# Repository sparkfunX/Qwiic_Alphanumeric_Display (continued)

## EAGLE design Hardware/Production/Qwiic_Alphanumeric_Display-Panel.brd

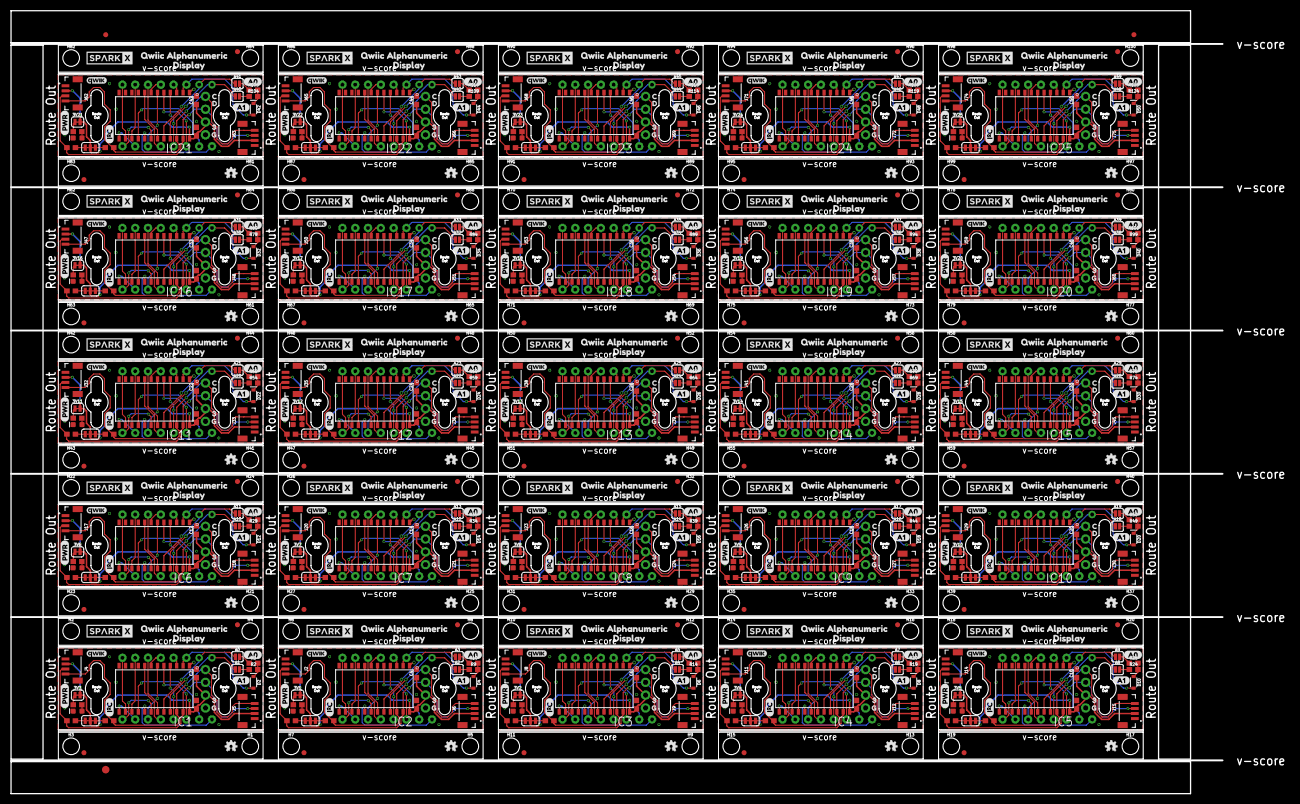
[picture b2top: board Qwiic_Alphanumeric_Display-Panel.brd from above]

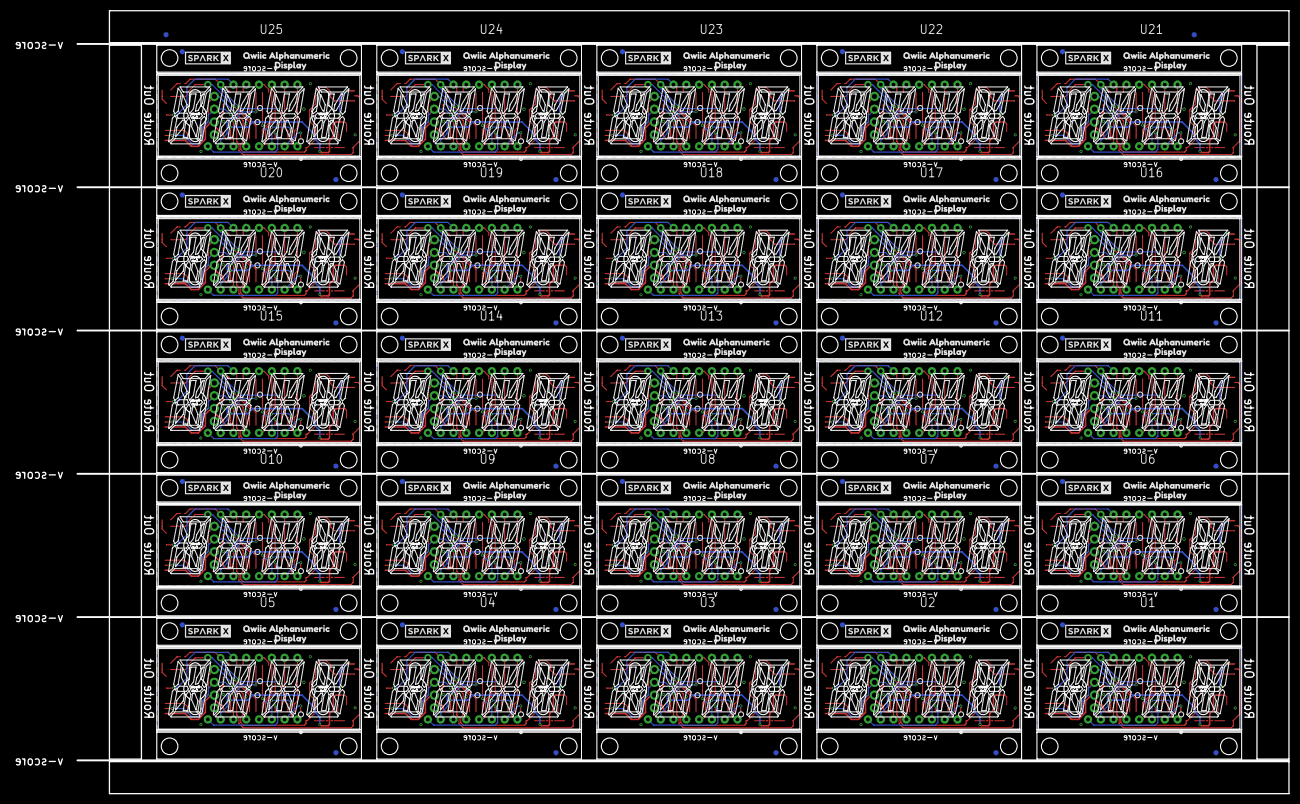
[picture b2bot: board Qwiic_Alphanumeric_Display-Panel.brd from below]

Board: 2 copper layers, 240.5 x 155.4 mm, 1105 parts (152 on the bottom side), 675 nets.

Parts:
3V1, 3V2, 3V3, 3V4, 3V5, 3V6, 3V7, 3V8, 3V9, 3V10, 3V11, 3V12, 3V13, 3V14, 3V15, 3V16, 3V17, 3V18, 3V19, 3V20, 3V21, 3V22, 3V23, 3V24, 3V25: JUMPER-SMT_2_NC_TRACE_SILK; SMT-JUMPER_2_NC_TRACE_SILK
A0, A1, A2, A3, A4, A5, A6, A7, A8, A9, A10, A11, A12, A13, A14, A15, A16, A17, A18, A19, A20, A21, A22, A23, A24, A25, A26, A27, A28, A29, A30, A31, A32, A33, A34, A35, A36, A37, A38, A39, A40, A41, A42, A43, A44, A45, A46, A47, A48, A49: JUMPER-SMT_2_NO_SILK; SMT-JUMPER_2_NO_SILK
C1, C3, C5, C7, C9, C11, C13, C15, C17, C19, C21, C23, C25, C27, C29, C31, C33, C35, C37, C39, C41, C43, C45, C47, C49: 0.1uF; 0603
C2, C4, C6, C8, C10, C12, C14, C16, C18, C20, C22, C24, C26, C28, C30, C32, C34, C36, C38, C40, C42, C44, C46, C48, C50: 10uF; 0603
D1, D3, D5, D7, D9, D11, D13, D15, D17, D19, D21, D23, D25, D27, D29, D31, D33, D35, D37, D39, D41, D43, D45, D47, D49: RED; LED-0603
D2, D4, D6, D8, D10, D12, D14, D16, D18, D20, D22, D24, D26, D28, D30, D32, D34, D36, D38, D40, D42, D44, D46, D48, D50: 250mA/100V; SOD-323
E$1, E$2, E$3, E$4: FIDUCIAL-1X2
E$5: FIDUCIAL-1.5X3
FD1, FD2, FD3, FD4, FD5, FD6, FD7, FD8, FD9, FD10, FD11, FD12, FD13, FD14, FD15, FD16, FD17, FD18, FD19, FD20, FD21, FD22, FD23, FD24, FD25, FD26, FD27, FD28, FD29, FD30, FD31, FD32, FD33, FD34, FD35, FD36, FD37, FD38, FD39, FD40, FD41, FD42, FD43, FD44, FD45, FD46, FD47, FD48, FD49, FD50, FD51, FD52, FD53, FD54, FD55, FD56, FD57, FD58, FD59, FD60, FD61, FD62, FD63, FD64, FD65, FD66, FD67, FD68, FD69, FD70, FD71, FD72, FD73, FD74, FD75, FD76, FD77, FD78, FD79, FD80, FD81, FD82, FD83, FD84, FD85, FD86, FD87, FD88, FD89, FD90, FD91, FD92, FD93, FD94, FD95, FD96, FD97, FD98, FD99, FD100: FIDUCIAL1X2; FIDUCIAL-1X2
H1, H2, H3, H4, H5, H6, H7, H8, H9, H10, H11, H12, H13, H14, H15, H16, H17, H18, H19, H20, H21, H22, H23, H24, H25, H26, H27, H28, H29, H30, H31, H32, H33, H34, H35, H36, H37, H38, H39, H40, H41, H42, H43, H44, H45, H46, H47, H48, H49, H50, H51, H52, H53, H54, H55, H56, H57, H58, H59, H60, H61, H62, H63, H64, H65, H66, H67, H68, H69, H70, H71, H72, H73, H74, H75, H76, H77, H78, H79, H80, H81, H82, H83, H84, H85, H86, H87, H88, H89, H90, H91, H92, H93, H94, H95, H96, H97, H98, H99, H100: STAND-OFF
I2C, I2C1, I2C2, I2C3, I2C4, I2C5, I2C6, I2C7, I2C8, I2C9, I2C10, I2C11, I2C12, I2C13, I2C14, I2C15, I2C16, I2C17, I2C18, I2C19, I2C20, I2C21, I2C22, I2C23, I2C24: JUMPER-SMT_3_2-NC_TRACE_SILK; SMT-JUMPER_3_2-NC_TRACE_SILK
IC1, IC2, IC3, IC4, IC5, IC6, IC7, IC8, IC9, IC10, IC11, IC12, IC13, IC14, IC15, IC16, IC17, IC18, IC19, IC20, IC21, IC22, IC23, IC24, IC25: HT16K33
J1, J3, J7, J10, J13, J16, J19, J22, J25, J28, J31, J34, J37, J40, J43, J46, J49, J52, J55, J58, J61, J64, J67, J70, J73: 1X04_NO_SILK
J2, J4, J5, J6, J8, J9, J11, J12, J14, J15, J17, J18, J20, J21, J23, J24, J26, J27, J29, J30, J32, J33, J35, J36, J38, J39, J41, J42, J44, J45, J47, J48, J50, J51, J53, J54, J56, J57, J59, J60, J62, J63, J65, J66, J68, J69, J71, J72, J74, J75: Vertical Qwiic Connector; JST04_1MM_VERT
LOGO1, LOGO2, LOGO3, LOGO4, LOGO5, LOGO6, LOGO7, LOGO8, LOGO9, LOGO10, LOGO11, LOGO12, LOGO13, LOGO14, LOGO15, LOGO16, LOGO17, LOGO18, LOGO19, LOGO20, LOGO21, LOGO22, LOGO23, LOGO24, LOGO25: OSHW-LOGOMINI; OSHW-LOGO-MINI
R1, R6, R11, R16, R21, R26, R31, R36, R41, R46, R51, R56, R61, R66, R71, R76, R81, R86, R91, R96, R101, R106, R111, R116, R121: 1k; 0603
R2, R3, R9, R10, R14, R15, R19, R20, R24, R25, R29, R30, R34, R35, R39, R40, R44, R45, R49, R50, R54, R55, R59, R60, R64, R65, R69, R70, R74, R75, R79, R80, R84, R85, R89, R90, R94, R95, R99, R100, R104, R105, R109, R110, R114, R115, R119, R120, R124, R125: 39k; 0603
R4, R5, R7, R8, R12, R13, R17, R18, R22, R23, R27, R28, R32, R33, R37, R38, R42, R43, R47, R48, R52, R53, R57, R58, R62, R63, R67, R68, R72, R73, R77, R78, R82, R83, R87, R88, R92, R93, R97, R98, R102, R103, R107, R108, R112, R113, R117, R118, R122, R123: 2.2k; 0603
U1, U2, U3, U4, U5, U6, U7, U8, U9, U10, U11, U12, U13, U14, U15, U16, U17, U18, U19, U20, U21, U22, U23, U24, U25: SILSMART_DISPLAY
U$1, U$29, U$46, U$63, U$80, U$97, U$114, U$131, U$148, U$165, U$182, U$199, U$216, U$233, U$250, U$267, U$284, U$301, U$318, U$335, U$352, U$369, U$386, U$403, U$420: 32
U$2, U$30, U$47, U$64, U$81, U$98, U$115, U$132, U$149, U$166, U$183, U$200, U$217, U$234, U$251, U$268, U$285, U$302, U$319, U$336, U$353, U$370, U$387, U$404, U$421: C0
U$3, U$9, U$35, U$52, U$69, U$86, U$103, U$120, U$137, U$154, U$171, U$188, U$205, U$222, U$239, U$256, U$273, U$290, U$307, U$324, U$341, U$358, U$375, U$392, U$409: PWR5
U$4, U$31, U$48, U$65, U$82, U$99, U$116, U$133, U$150, U$167, U$184, U$201, U$218, U$235, U$252, U$269, U$286, U$303, U$320, U$337, U$354, U$371, U$388, U$405, U$422: D1
U$5, U$32, U$49, U$66, U$83, U$100, U$117, U$134, U$151, U$168, U$185, U$202, U$219, U$236, U$253, U$270, U$287, U$304, U$321, U$338, U$355, U$372, U$389, U$406, U$423: G3
U$6, U$28, U$45, U$62, U$79, U$96, U$113, U$130, U$147, U$164, U$181, U$198, U$215, U$232, U$249, U$266, U$283, U$300, U$317, U$334, U$351, U$368, U$385, U$402, U$419: QWIIC_4MM
U$7, U$8, U$33, U$34, U$50, U$51, U$67, U$68, U$84, U$85, U$101, U$102, U$118, U$119, U$135, U$136, U$152, U$153, U$169, U$170, U$186, U$187, U$203, U$204, U$220, U$221, U$237, U$238, U$254, U$255, U$271, U$272, U$288, U$289, U$305, U$306, U$322, U$323, U$339, U$340, U$356, U$357, U$373, U$374, U$390, U$391, U$407, U$408, U$424, U$425: SPARKX-LOGO4; SPARKX-MEDIUM
U$10, U$11, U$36, U$53, U$70, U$87, U$104, U$121, U$138, U$155, U$172, U$189, U$206, U$223, U$240, U$257, U$274, U$291, U$308, U$325, U$342, U$359, U$376, U$393, U$410: I_SUPER2_C-()-04
U$12, U$13, U$15, U$22, U$37, U$39, U$54, U$56, U$71, U$73, U$88, U$90, U$105, U$107, U$122, U$124, U$139, U$141, U$156, U$158, U$173, U$175, U$190, U$192, U$207, U$209, U$224, U$226, U$241, U$243, U$258, U$260, U$275, U$277, U$292, U$294, U$309, U$311, U$326, U$328, U$343, U$345, U$360, U$362, U$377, U$379, U$394, U$396, U$411, U$413: QWIIC_ALPHANUMERIC0
U$14, U$16, U$17, U$23, U$38, U$40, U$55, U$57, U$72, U$74, U$89, U$91, U$106, U$108, U$123, U$125, U$140, U$142, U$157, U$159, U$174, U$176, U$191, U$193, U$208, U$210, U$225, U$227, U$242, U$244, U$259, U$261, U$276, U$278, U$293, U$295, U$310, U$312, U$327, U$329, U$344, U$346, U$361, U$363, U$378, U$380, U$395, U$397, U$412, U$414: DISPLAY1
U$18, U$19, U$24, U$25, U$41, U$42, U$58, U$59, U$75, U$76, U$92, U$93, U$109, U$110, U$126, U$127, U$143, U$144, U$160, U$161, U$177, U$178, U$194, U$195, U$211, U$212, U$228, U$229, U$245, U$246, U$262, U$263, U$279, U$280, U$296, U$297, U$313, U$314, U$330, U$331, U$347, U$348, U$364, U$365, U$381, U$382, U$398, U$399, U$415, U$416: MOUNTING_HOLE_M2-0.4X6
U$20, U$26, U$43, U$60, U$77, U$94, U$111, U$128, U$145, U$162, U$179, U$196, U$213, U$230, U$247, U$264, U$281, U$298, U$315, U$332, U$349, U$366, U$383, U$400, U$417: A00
U$21, U$27, U$44, U$61, U$78, U$95, U$112, U$129, U$146, U$163, U$180, U$197, U$214, U$231, U$248, U$265, U$282, U$299, U$316, U$333, U$350, U$367, U$384, U$401, U$418: A11

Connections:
3.3V: 3V3.2, C1.1, C2.1, I2C.2, IC1.24, J3.2, J4.2, J5.2
3.3V1: 3V1.2, C3.1, C4.1, I2C1.2, IC2.24, J1.2, J2.2, J6.2
3.3V2: 3V2.2, C5.1, C6.1, I2C2.2, IC3.24, J7.2, J8.2, J9.2
3.3V3: 3V4.2, C7.1, C8.1, I2C3.2, IC4.24, J10.2, J11.2, J12.2
3.3V4: 3V5.2, C9.1, C10.1, I2C4.2, IC5.24, J13.2, J14.2, J15.2
3.3V5: 3V6.2, C11.1, C12.1, I2C5.2, IC6.24, J16.2, J17.2, J18.2
3.3V6: 3V7.2, C13.1, C14.1, I2C6.2, IC7.24, J19.2, J20.2, J21.2
3.3V7: 3V8.2, C15.1, C16.1, I2C7.2, IC8.24, J22.2, J23.2, J24.2
3.3V8: 3V9.2, C17.1, C18.1, I2C8.2, IC9.24, J25.2, J26.2, J27.2
3.3V9: 3V10.2, C19.1, C20.1, I2C9.2, IC10.24, J28.2, J29.2, J30.2
3.3V10: 3V11.2, C21.1, C22.1, I2C10.2, IC11.24, J31.2, J32.2, J33.2
3.3V11: 3V12.2, C23.1, C24.1, I2C11.2, IC12.24, J34.2, J35.2, J36.2
3.3V12: 3V13.2, C25.1, C26.1, I2C12.2, IC13.24, J37.2, J38.2, J39.2
3.3V13: 3V14.2, C27.1, C28.1, I2C13.2, IC14.24, J40.2, J41.2, J42.2
3.3V14: 3V15.2, C29.1, C30.1, I2C14.2, IC15.24, J43.2, J44.2, J45.2
3.3V15: 3V16.2, C31.1, C32.1, I2C15.2, IC16.24, J46.2, J47.2, J48.2
3.3V16: 3V17.2, C33.1, C34.1, I2C16.2, IC17.24, J49.2, J50.2, J51.2
3.3V17: 3V18.2, C35.1, C36.1, I2C17.2, IC18.24, J52.2, J53.2, J54.2
3.3V18: 3V19.2, C37.1, C38.1, I2C18.2, IC19.24, J55.2, J56.2, J57.2
3.3V19: 3V20.2, C39.1, C40.1, I2C19.2, IC20.24, J58.2, J59.2, J60.2
3.3V20: 3V21.2, C41.1, C42.1, I2C20.2, IC21.24, J61.2, J62.2, J63.2
3.3V21: 3V22.2, C43.1, C44.1, I2C21.2, IC22.24, J64.2, J65.2, J66.2
3.3V22: 3V23.2, C45.1, C46.1, I2C22.2, IC23.24, J67.2, J68.2, J69.2
3.3V23: 3V24.2, C47.1, C48.1, I2C23.2, IC24.24, J70.2, J71.2, J72.2
3.3V24: 3V25.2, C49.1, C50.1, I2C24.2, IC25.24, J73.2, J74.2, J75.2
COM_A: D2.A, IC1.2, U1.14
COM_A1: D4.A, IC2.2, U2.14
COM_A2: D6.A, IC3.2, U3.14
COM_A3: D8.A, IC4.2, U4.14
COM_A4: D10.A, IC5.2, U5.14
COM_A5: D12.A, IC6.2, U6.14
COM_A6: D14.A, IC7.2, U7.14
COM_A7: D16.A, IC8.2, U8.14
COM_A8: D18.A, IC9.2, U9.14
COM_A9: D20.A, IC10.2, U10.14
COM_A10: D22.A, IC11.2, U11.14
COM_A11: D24.A, IC12.2, U12.14
COM_A12: D26.A, IC13.2, U13.14
COM_A13: D28.A, IC14.2, U14.14
COM_A14: D30.A, IC15.2, U15.14
COM_A15: D32.A, IC16.2, U16.14
COM_A16: D34.A, IC17.2, U17.14
COM_A17: D36.A, IC18.2, U18.14
COM_A18: D38.A, IC19.2, U19.14
COM_A19: D40.A, IC20.2, U20.14
COM_A20: D42.A, IC21.2, U21.14
COM_A21: D44.A, IC22.2, U22.14
COM_A22: D46.A, IC23.2, U23.14
COM_A23: D48.A, IC24.2, U24.14
COM_A24: D50.A, IC25.2, U25.14
COM_B: IC1.3, U1.13
COM_B1: IC2.3, U2.13
COM_B2: IC3.3, U3.13
COM_B3: IC4.3, U4.13
COM_B4: IC5.3, U5.13
COM_B5: IC6.3, U6.13
COM_B6: IC7.3, U7.13
COM_B7: IC8.3, U8.13
COM_B8: IC9.3, U9.13
COM_B9: IC10.3, U10.13
COM_B10: IC11.3, U11.13
COM_B11: IC12.3, U12.13
COM_B12: IC13.3, U13.13
COM_B13: IC14.3, U14.13
COM_B14: IC15.3, U15.13
COM_B15: IC16.3, U16.13
COM_B16: IC17.3, U17.13
COM_B17: IC18.3, U18.13
COM_B18: IC19.3, U19.13
COM_B19: IC20.3, U20.13
COM_B20: IC21.3, U21.13
COM_B21: IC22.3, U22.13
COM_B22: IC23.3, U23.13
COM_B23: IC24.3, U24.13
COM_B24: IC25.3, U25.13
COM_C: IC1.4, U1.4
COM_C1: IC2.4, U2.4
COM_C2: IC3.4, U3.4
COM_C3: IC4.4, U4.4
COM_C4: IC5.4, U5.4
COM_C5: IC6.4, U6.4
COM_C6: IC7.4, U7.4
COM_C7: IC8.4, U8.4
COM_C8: IC9.4, U9.4
COM_C9: IC10.4, U10.4
COM_C10: IC11.4, U11.4
COM_C11: IC12.4, U12.4
COM_C12: IC13.4, U13.4
COM_C13: IC14.4, U14.4
COM_C14: IC15.4, U15.4
COM_C15: IC16.4, U16.4
COM_C16: IC17.4, U17.4
COM_C17: IC18.4, U18.4
COM_C18: IC19.4, U19.4
COM_C19: IC20.4, U20.4
COM_C20: IC21.4, U21.4
COM_C21: IC22.4, U22.4
COM_C22: IC23.4, U23.4
COM_C23: IC24.4, U24.4
COM_C24: IC25.4, U25.4
COM_D: IC1.5, U1.3
COM_D1: IC2.5, U2.3
COM_D2: IC3.5, U3.3
COM_D3: IC4.5, U4.3
COM_D4: IC5.5, U5.3
COM_D5: IC6.5, U6.3
COM_D6: IC7.5, U7.3
COM_D7: IC8.5, U8.3
COM_D8: IC9.5, U9.3
COM_D9: IC10.5, U10.3
COM_D10: IC11.5, U11.3
COM_D11: IC12.5, U12.3
COM_D12: IC13.5, U13.3
COM_D13: IC14.5, U14.3
COM_D14: IC15.5, U15.3
COM_D15: IC16.5, U16.3
COM_D16: IC17.5, U17.3
COM_D17: IC18.5, U18.3
COM_D18: IC19.5, U19.3
COM_D19: IC20.5, U20.3
COM_D20: IC21.5, U21.3
COM_D21: IC22.5, U22.3
COM_D22: IC23.5, U23.3
COM_D23: IC24.5, U24.3
COM_D24: IC25.5, U25.3
COM_E: IC1.6, U1.6
COM_E1: IC2.6, U2.6
COM_E2: IC3.6, U3.6
COM_E3: IC4.6, U4.6
COM_E4: IC5.6, U5.6
COM_E5: IC6.6, U6.6
COM_E6: IC7.6, U7.6
COM_E7: IC8.6, U8.6
COM_E8: IC9.6, U9.6
COM_E9: IC10.6, U10.6
COM_E10: IC11.6, U11.6
COM_E11: IC12.6, U12.6
COM_E12: IC13.6, U13.6
COM_E13: IC14.6, U14.6
COM_E14: IC15.6, U15.6
COM_E15: IC16.6, U16.6
COM_E16: IC17.6, U17.6
COM_E17: IC18.6, U18.6
COM_E18: IC19.6, U19.6
COM_E19: IC20.6, U20.6
COM_E20: IC21.6, U21.6
COM_E21: IC22.6, U22.6
COM_E22: IC23.6, U23.6
COM_E23: IC24.6, U24.6
COM_E24: IC25.6, U25.6
COM_F: IC1.7, U1.12
COM_F1: IC2.7, U2.12
COM_F2: IC3.7, U3.12
COM_F3: IC4.7, U4.12
COM_F4: IC5.7, U5.12
COM_F5: IC6.7, U6.12
COM_F6: IC7.7, U7.12
COM_F7: IC8.7, U8.12
COM_F8: IC9.7, U9.12
COM_F9: IC10.7, U10.12
COM_F10: IC11.7, U11.12
COM_F11: IC12.7, U12.12
COM_F12: IC13.7, U13.12
COM_F13: IC14.7, U14.12
COM_F14: IC15.7, U15.12
COM_F15: IC16.7, U16.12
COM_F16: IC17.7, U17.12
COM_F17: IC18.7, U18.12
COM_F18: IC19.7, U19.12
COM_F19: IC20.7, U20.12
COM_F20: IC21.7, U21.12
COM_F21: IC22.7, U22.12
COM_F22: IC23.7, U23.12
COM_F23: IC24.7, U24.12
COM_F24: IC25.7, U25.12
COM_G: IC1.8, U1.5
COM_G1: IC2.8, U2.5
COM_G2: IC3.8, U3.5
COM_G3: IC4.8, U4.5
COM_G4: IC5.8, U5.5
COM_G5: IC6.8, U6.5
COM_G6: IC7.8, U7.5
COM_G7: IC8.8, U8.5
COM_G8: IC9.8, U9.5
COM_G9: IC10.8, U10.5
COM_G10: IC11.8, U11.5
COM_G11: IC12.8, U12.5
COM_G12: IC13.8, U13.5
COM_G13: IC14.8, U14.5
COM_G14: IC15.8, U15.5
COM_G15: IC16.8, U16.5
COM_G16: IC17.8, U17.5
COM_G17: IC18.8, U18.5
COM_G18: IC19.8, U19.5
COM_G19: IC20.8, U20.5
COM_G20: IC21.8, U21.5
COM_G21: IC22.8, U22.5
COM_G22: IC23.8, U23.5
COM_G23: IC24.8, U24.5
COM_G24: IC25.8, U25.5
DIG_1A: A1.1, IC1.21, U1.16
DIG_1A1: A2.1, IC2.21, U2.16
DIG_1A2: A4.1, IC3.21, U3.16
DIG_1A3: A6.1, IC4.21, U4.16
DIG_1A4: A8.1, IC5.21, U5.16
DIG_1A5: A10.1, IC6.21, U6.16
DIG_1A6: A12.1, IC7.21, U7.16
DIG_1A7: A14.1, IC8.21, U8.16
DIG_1A8: A16.1, IC9.21, U9.16
DIG_1A9: A18.1, IC10.21, U10.16
DIG_1A10: A20.1, IC11.21, U11.16
DIG_1A11: A22.1, IC12.21, U12.16
DIG_1A12: A24.1, IC13.21, U13.16
DIG_1A13: A26.1, IC14.21, U14.16
DIG_1A14: A28.1, IC15.21, U15.16
DIG_1A15: A30.1, IC16.21, U16.16
DIG_1A16: A32.1, IC17.21, U17.16
DIG_1A17: A34.1, IC18.21, U18.16
DIG_1A18: A36.1, IC19.21, U19.16
DIG_1A19: A38.1, IC20.21, U20.16
DIG_1A20: A40.1, IC21.21, U21.16
DIG_1A21: A42.1, IC22.21, U22.16
DIG_1A22: A44.1, IC23.21, U23.16
DIG_1A23: A46.1, IC24.21, U24.16
DIG_1A24: A48.1, IC25.21, U25.16
DIG_1B: IC1.17, U1.1
DIG_1B1: IC2.17, U2.1
DIG_1B2: IC3.17, U3.1
DIG_1B3: IC4.17, U4.1
DIG_1B4: IC5.17, U5.1
DIG_1B5: IC6.17, U6.1
DIG_1B6: IC7.17, U7.1
DIG_1B7: IC8.17, U8.1
DIG_1B8: IC9.17, U9.1
DIG_1B9: IC10.17, U10.1
DIG_1B10: IC11.17, U11.1
DIG_1B11: IC12.17, U12.1
DIG_1B12: IC13.17, U13.1
DIG_1B13: IC14.17, U14.1
DIG_1B14: IC15.17, U15.1
DIG_1B15: IC16.17, U16.1
DIG_1B16: IC17.17, U17.1
DIG_1B17: IC18.17, U18.1
DIG_1B18: IC19.17, U19.1
DIG_1B19: IC20.17, U20.1
DIG_1B20: IC21.17, U21.1
DIG_1B21: IC22.17, U22.1
DIG_1B22: IC23.17, U23.1
DIG_1B23: IC24.17, U24.1
DIG_1B24: IC25.17, U25.1
DIG_2A: A0.1, IC1.20, U1.15
DIG_2A1: A3.1, IC2.20, U2.15
DIG_2A2: A5.1, IC3.20, U3.15
DIG_2A3: A7.1, IC4.20, U4.15
DIG_2A4: A9.1, IC5.20, U5.15
DIG_2A5: A11.1, IC6.20, U6.15
DIG_2A6: A13.1, IC7.20, U7.15
DIG_2A7: A15.1, IC8.20, U8.15
DIG_2A8: A17.1, IC9.20, U9.15
DIG_2A9: A19.1, IC10.20, U10.15
DIG_2A10: A21.1, IC11.20, U11.15
DIG_2A11: A23.1, IC12.20, U12.15
DIG_2A12: A25.1, IC13.20, U13.15
DIG_2A13: A27.1, IC14.20, U14.15
DIG_2A14: A29.1, IC15.20, U15.15
DIG_2A15: A31.1, IC16.20, U16.15
DIG_2A16: A33.1, IC17.20, U17.15
DIG_2A17: A35.1, IC18.20, U18.15
DIG_2A18: A37.1, IC19.20, U19.15
DIG_2A19: A39.1, IC20.20, U20.15
DIG_2A20: A41.1, IC21.20, U21.15
DIG_2A21: A43.1, IC22.20, U22.15
DIG_2A22: A45.1, IC23.20, U23.15
DIG_2A23: A47.1, IC24.20, U24.15
DIG_2A24: A49.1, IC25.20, U25.15
DIG_2B: IC1.16, U1.2
DIG_2B1: IC2.16, U2.2
DIG_2B2: IC3.16, U3.2
DIG_2B3: IC4.16, U4.2
DIG_2B4: IC5.16, U5.2
DIG_2B5: IC6.16, U6.2
DIG_2B6: IC7.16, U7.2
DIG_2B7: IC8.16, U8.2
DIG_2B8: IC9.16, U9.2
DIG_2B9: IC10.16, U10.2
DIG_2B10: IC11.16, U11.2
DIG_2B11: IC12.16, U12.2
DIG_2B12: IC13.16, U13.2
DIG_2B13: IC14.16, U14.2
DIG_2B14: IC15.16, U15.2
DIG_2B15: IC16.16, U16.2
DIG_2B16: IC17.16, U17.2
DIG_2B17: IC18.16, U18.2
DIG_2B18: IC19.16, U19.2
DIG_2B19: IC20.16, U20.2
DIG_2B20: IC21.16, U21.2
DIG_2B21: IC22.16, U22.2
DIG_2B22: IC23.16, U23.2
DIG_2B23: IC24.16, U24.2
DIG_2B24: IC25.16, U25.2
DIG_3A: IC1.19, U1.11
DIG_3A1: IC2.19, U2.11
DIG_3A2: IC3.19, U3.11
DIG_3A3: IC4.19, U4.11
DIG_3A4: IC5.19, U5.11
DIG_3A5: IC6.19, U6.11
DIG_3A6: IC7.19, U7.11
DIG_3A7: IC8.19, U8.11
DIG_3A8: IC9.19, U9.11
DIG_3A9: IC10.19, U10.11
DIG_3A10: IC11.19, U11.11
DIG_3A11: IC12.19, U12.11
DIG_3A12: IC13.19, U13.11
DIG_3A13: IC14.19, U14.11
DIG_3A14: IC15.19, U15.11
DIG_3A15: IC16.19, U16.11
DIG_3A16: IC17.19, U17.11
DIG_3A17: IC18.19, U18.11
DIG_3A18: IC19.19, U19.11
DIG_3A19: IC20.19, U20.11
DIG_3A20: IC21.19, U21.11
DIG_3A21: IC22.19, U22.11
DIG_3A22: IC23.19, U23.11
DIG_3A23: IC24.19, U24.11
DIG_3A24: IC25.19, U25.11
DIG_3B: IC1.15, U1.10
DIG_3B1: IC2.15, U2.10
DIG_3B2: IC3.15, U3.10
DIG_3B3: IC4.15, U4.10
DIG_3B4: IC5.15, U5.10
DIG_3B5: IC6.15, U6.10
DIG_3B6: IC7.15, U7.10
DIG_3B7: IC8.15, U8.10
DIG_3B8: IC9.15, U9.10
DIG_3B9: IC10.15, U10.10
DIG_3B10: IC11.15, U11.10
DIG_3B11: IC12.15, U12.10
DIG_3B12: IC13.15, U13.10
DIG_3B13: IC14.15, U14.10
DIG_3B14: IC15.15, U15.10
DIG_3B15: IC16.15, U16.10
DIG_3B16: IC17.15, U17.10
DIG_3B17: IC18.15, U18.10
DIG_3B18: IC19.15, U19.10
DIG_3B19: IC20.15, U20.10
DIG_3B20: IC21.15, U21.10
DIG_3B21: IC22.15, U22.10
DIG_3B22: IC23.15, U23.10
DIG_3B23: IC24.15, U24.10
DIG_3B24: IC25.15, U25.10
DIG_4A: IC1.18, U1.8
DIG_4A1: IC2.18, U2.8
DIG_4A2: IC3.18, U3.8
DIG_4A3: IC4.18, U4.8
DIG_4A4: IC5.18, U5.8
DIG_4A5: IC6.18, U6.8
DIG_4A6: IC7.18, U7.8
DIG_4A7: IC8.18, U8.8
DIG_4A8: IC9.18, U9.8
DIG_4A9: IC10.18, U10.8
DIG_4A10: IC11.18, U11.8
DIG_4A11: IC12.18, U12.8
DIG_4A12: IC13.18, U13.8
DIG_4A13: IC14.18, U14.8
DIG_4A14: IC15.18, U15.8
DIG_4A15: IC16.18, U16.8
DIG_4A16: IC17.18, U17.8
DIG_4A17: IC18.18, U18.8
DIG_4A18: IC19.18, U19.8
DIG_4A19: IC20.18, U20.8
DIG_4A20: IC21.18, U21.8
DIG_4A21: IC22.18, U22.8
DIG_4A22: IC23.18, U23.8
DIG_4A23: IC24.18, U24.8
DIG_4A24: IC25.18, U25.8
DIG_4B: IC1.14, U1.9
DIG_4B1: IC2.14, U2.9
DIG_4B2: IC3.14, U3.9
DIG_4B3: IC4.14, U4.9
DIG_4B4: IC5.14, U5.9
DIG_4B5: IC6.14, U6.9
DIG_4B6: IC7.14, U7.9
DIG_4B7: IC8.14, U8.9
DIG_4B8: IC9.14, U9.9
DIG_4B9: IC10.14, U10.9
DIG_4B10: IC11.14, U11.9
DIG_4B11: IC12.14, U12.9
DIG_4B12: IC13.14, U13.9
DIG_4B13: IC14.14, U14.9
DIG_4B14: IC15.14, U15.9
DIG_4B15: IC16.14, U16.9
DIG_4B16: IC17.14, U17.9
DIG_4B17: IC18.14, U18.9
DIG_4B18: IC19.14, U19.9
DIG_4B19: IC20.14, U20.9
DIG_4B20: IC21.14, U21.9
DIG_4B21: IC22.14, U22.9
DIG_4B22: IC23.14, U23.9
DIG_4B23: IC24.14, U24.9
DIG_4B24: IC25.14, U25.9
DIG_DP: IC1.13, U1.7
DIG_DP1: IC2.13, U2.7
DIG_DP2: IC3.13, U3.7
DIG_DP3: IC4.13, U4.7
DIG_DP4: IC5.13, U5.7
DIG_DP5: IC6.13, U6.7
DIG_DP6: IC7.13, U7.7
DIG_DP7: IC8.13, U8.7
DIG_DP8: IC9.13, U9.7
DIG_DP9: IC10.13, U10.7
DIG_DP10: IC11.13, U11.7
DIG_DP11: IC12.13, U12.7
DIG_DP12: IC13.13, U13.7
DIG_DP13: IC14.13, U14.7
DIG_DP14: IC15.13, U15.7
DIG_DP15: IC16.13, U16.7
DIG_DP16: IC17.13, U17.7
DIG_DP17: IC18.13, U18.7
DIG_DP18: IC19.13, U19.7
DIG_DP19: IC20.13, U20.7
DIG_DP20: IC21.13, U21.7
DIG_DP21: IC22.13, U22.7
DIG_DP22: IC23.13, U23.7
DIG_DP23: IC24.13, U24.7
DIG_DP24: IC25.13, U25.7
GND: C1.2, C2.2, D1.C, IC1.1, J3.1, J4.1, J5.1
GND1: C3.2, C4.2, D3.C, IC2.1, J1.1, J2.1, J6.1
GND2: C5.2, C6.2, D5.C, IC3.1, J7.1, J8.1, J9.1
GND3: C7.2, C8.2, D7.C, IC4.1, J10.1, J11.1, J12.1
GND4: C9.2, C10.2, D9.C, IC5.1, J13.1, J14.1, J15.1
GND5: C11.2, C12.2, D11.C, IC6.1, J16.1, J17.1, J18.1
GND6: C13.2, C14.2, D13.C, IC7.1, J19.1, J20.1, J21.1
GND7: C15.2, C16.2, D15.C, IC8.1, J22.1, J23.1, J24.1
GND8: C17.2, C18.2, D17.C, IC9.1, J25.1, J26.1, J27.1
GND9: C19.2, C20.2, D19.C, IC10.1, J28.1, J29.1, J30.1
GND10: C21.2, C22.2, D21.C, IC11.1, J31.1, J32.1, J33.1
GND11: C23.2, C24.2, D23.C, IC12.1, J34.1, J35.1, J36.1
GND12: C25.2, C26.2, D25.C, IC13.1, J37.1, J38.1, J39.1
GND13: C27.2, C28.2, D27.C, IC14.1, J40.1, J41.1, J42.1
GND14: C29.2, C30.2, D29.C, IC15.1, J43.1, J44.1, J45.1
GND15: C31.2, C32.2, D31.C, IC16.1, J46.1, J47.1, J48.1
GND16: C33.2, C34.2, D33.C, IC17.1, J49.1, J50.1, J51.1
GND17: C35.2, C36.2, D35.C, IC18.1, J52.1, J53.1, J54.1
GND18: C37.2, C38.2, D37.C, IC19.1, J55.1, J56.1, J57.1
GND19: C39.2, C40.2, D39.C, IC20.1, J58.1, J59.1, J60.1
GND20: C41.2, C42.2, D41.C, IC21.1, J61.1, J62.1, J63.1
GND21: C43.2, C44.2, D43.C, IC22.1, J64.1, J65.1, J66.1
GND22: C45.2, C46.2, D45.C, IC23.1, J67.1, J68.1, J69.1
GND23: C47.2, C48.2, D47.C, IC24.1, J70.1, J71.1, J72.1
GND24: C49.2, C50.2, D49.C, IC25.1, J73.1, J74.1, J75.1
unnamed: D1.A, R1.1
unnamed: A1.2, R2.1
unnamed: A0.2, R3.1
unnamed: I2C.1, R5.2
unnamed: I2C.3, R4.2
unnamed: D2.C, R2.2, R3.2
unnamed: 3V3.1, R1.2
unnamed: D3.A, R6.1
unnamed: I2C1.1, R8.2
unnamed: I2C1.3, R7.2
unnamed: A2.2, R9.1
unnamed: A3.2, R10.1
unnamed: D4.C, R9.2, R10.2
unnamed: 3V1.1, R6.2
unnamed: D5.A, R11.1
unnamed: I2C2.1, R13.2
unnamed: I2C2.3, R12.2
unnamed: A4.2, R14.1
unnamed: A5.2, R15.1
unnamed: D6.C, R14.2, R15.2
unnamed: 3V2.1, R11.2
unnamed: D7.A, R16.1
unnamed: I2C3.1, R18.2
unnamed: I2C3.3, R17.2
unnamed: A6.2, R19.1
unnamed: A7.2, R20.1
unnamed: D8.C, R19.2, R20.2
unnamed: 3V4.1, R16.2
unnamed: D9.A, R21.1
unnamed: I2C4.1, R23.2
unnamed: I2C4.3, R22.2
unnamed: A8.2, R24.1
unnamed: A9.2, R25.1
unnamed: D10.C, R24.2, R25.2
unnamed: 3V5.1, R21.2
unnamed: D11.A, R26.1
unnamed: I2C5.1, R28.2
unnamed: I2C5.3, R27.2
unnamed: A10.2, R29.1
unnamed: A11.2, R30.1
unnamed: D12.C, R29.2, R30.2
unnamed: 3V6.1, R26.2
unnamed: D13.A, R31.1
unnamed: I2C6.1, R33.2
unnamed: I2C6.3, R32.2
unnamed: A12.2, R34.1
unnamed: A13.2, R35.1
unnamed: D14.C, R34.2, R35.2
unnamed: 3V7.1, R31.2
unnamed: D15.A, R36.1
unnamed: I2C7.1, R38.2
unnamed: I2C7.3, R37.2
unnamed: A14.2, R39.1
unnamed: A15.2, R40.1
unnamed: D16.C, R39.2, R40.2
unnamed: 3V8.1, R36.2
unnamed: D17.A, R41.1
unnamed: I2C8.1, R43.2
unnamed: I2C8.3, R42.2
unnamed: A16.2, R44.1
unnamed: A17.2, R45.1
unnamed: D18.C, R44.2, R45.2
unnamed: 3V9.1, R41.2
unnamed: D19.A, R46.1
unnamed: I2C9.1, R48.2
unnamed: I2C9.3, R47.2
unnamed: A18.2, R49.1
unnamed: A19.2, R50.1
unnamed: D20.C, R49.2, R50.2
unnamed: 3V10.1, R46.2
unnamed: D21.A, R51.1
unnamed: I2C10.1, R53.2
unnamed: I2C10.3, R52.2
unnamed: A20.2, R54.1
unnamed: A21.2, R55.1
unnamed: D22.C, R54.2, R55.2
unnamed: 3V11.1, R51.2
unnamed: D23.A, R56.1
unnamed: I2C11.1, R58.2
unnamed: I2C11.3, R57.2
unnamed: A22.2, R59.1
unnamed: A23.2, R60.1
unnamed: D24.C, R59.2, R60.2
unnamed: 3V12.1, R56.2
unnamed: D25.A, R61.1
unnamed: I2C12.1, R63.2
unnamed: I2C12.3, R62.2
unnamed: A24.2, R64.1
unnamed: A25.2, R65.1
unnamed: D26.C, R64.2, R65.2
unnamed: 3V13.1, R61.2
unnamed: D27.A, R66.1
unnamed: I2C13.1, R68.2
unnamed: I2C13.3, R67.2
unnamed: A26.2, R69.1
unnamed: A27.2, R70.1
unnamed: D28.C, R69.2, R70.2
unnamed: 3V14.1, R66.2
unnamed: D29.A, R71.1
unnamed: I2C14.1, R73.2
unnamed: I2C14.3, R72.2
unnamed: A28.2, R74.1
unnamed: A29.2, R75.1
unnamed: D30.C, R74.2, R75.2
unnamed: 3V15.1, R71.2
unnamed: D31.A, R76.1
unnamed: I2C15.1, R78.2
unnamed: I2C15.3, R77.2
unnamed: A30.2, R79.1
unnamed: A31.2, R80.1
unnamed: D32.C, R79.2, R80.2
unnamed: 3V16.1, R76.2
unnamed: D33.A, R81.1
unnamed: I2C16.1, R83.2
unnamed: I2C16.3, R82.2
unnamed: A32.2, R84.1
unnamed: A33.2, R85.1
unnamed: D34.C, R84.2, R85.2
unnamed: 3V17.1, R81.2
unnamed: D35.A, R86.1
unnamed: I2C17.1, R88.2
unnamed: I2C17.3, R87.2
unnamed: A34.2, R89.1
unnamed: A35.2, R90.1
unnamed: D36.C, R89.2, R90.2
unnamed: 3V18.1, R86.2
unnamed: D37.A, R91.1
unnamed: I2C18.1, R93.2
unnamed: I2C18.3, R92.2
unnamed: A36.2, R94.1
unnamed: A37.2, R95.1
unnamed: D38.C, R94.2, R95.2
unnamed: 3V19.1, R91.2
unnamed: D39.A, R96.1
unnamed: I2C19.1, R98.2
unnamed: I2C19.3, R97.2
unnamed: A38.2, R99.1
unnamed: A39.2, R100.1
unnamed: D40.C, R99.2, R100.2
unnamed: 3V20.1, R96.2
unnamed: D41.A, R101.1
unnamed: I2C20.1, R103.2
unnamed: I2C20.3, R102.2
unnamed: A40.2, R104.1
unnamed: A41.2, R105.1
unnamed: D42.C, R104.2, R105.2
unnamed: 3V21.1, R101.2
unnamed: D43.A, R106.1
unnamed: I2C21.1, R108.2
unnamed: I2C21.3, R107.2
unnamed: A42.2, R109.1
unnamed: A43.2, R110.1
unnamed: D44.C, R109.2, R110.2
unnamed: 3V22.1, R106.2
unnamed: D45.A, R111.1
unnamed: I2C22.1, R113.2
unnamed: I2C22.3, R112.2
unnamed: A44.2, R114.1
unnamed: A45.2, R115.1
unnamed: D46.C, R114.2, R115.2
unnamed: 3V23.1, R111.2
unnamed: D47.A, R116.1
unnamed: I2C23.1, R118.2
unnamed: I2C23.3, R117.2
unnamed: A46.2, R119.1
unnamed: A47.2, R120.1
unnamed: D48.C, R119.2, R120.2
unnamed: 3V24.1, R116.2
unnamed: D49.A, R121.1
unnamed: I2C24.1, R123.2
unnamed: I2C24.3, R122.2
unnamed: A48.2, R124.1
unnamed: A49.2, R125.1
unnamed: D50.C, R124.2, R125.2
unnamed: 3V25.1, R121.2
SCL: IC1.22, J3.4, J4.4, J5.4, R5.1
SCL1: IC2.22, J1.4, J2.4, J6.4, R8.1
SCL2: IC3.22, J7.4, J8.4, J9.4, R13.1
SCL3: IC4.22, J10.4, J11.4, J12.4, R18.1
SCL4: IC5.22, J13.4, J14.4, J15.4, R23.1
SCL5: IC6.22, J16.4, J17.4, J18.4, R28.1
SCL6: IC7.22, J19.4, J20.4, J21.4, R33.1
SCL7: IC8.22, J22.4, J23.4, J24.4, R38.1
SCL8: IC9.22, J25.4, J26.4, J27.4, R43.1
SCL9: IC10.22, J28.4, J29.4, J30.4, R48.1
SCL10: IC11.22, J31.4, J32.4, J33.4, R53.1
SCL11: IC12.22, J34.4, J35.4, J36.4, R58.1
SCL12: IC13.22, J37.4, J38.4, J39.4, R63.1
SCL13: IC14.22, J40.4, J41.4, J42.4, R68.1
SCL14: IC15.22, J43.4, J44.4, J45.4, R73.1
SCL15: IC16.22, J46.4, J47.4, J48.4, R78.1
SCL16: IC17.22, J49.4, J50.4, J51.4, R83.1
SCL17: IC18.22, J52.4, J53.4, J54.4, R88.1
SCL18: IC19.22, J55.4, J56.4, J57.4, R93.1
SCL19: IC20.22, J58.4, J59.4, J60.4, R98.1
SCL20: IC21.22, J61.4, J62.4, J63.4, R103.1
SCL21: IC22.22, J64.4, J65.4, J66.4, R108.1
SCL22: IC23.22, J67.4, J68.4, J69.4, R113.1
SCL23: IC24.22, J70.4, J71.4, J72.4, R118.1
SCL24: IC25.22, J73.4, J74.4, J75.4, R123.1
SDA: IC1.23, J3.3, J4.3, J5.3, R4.1
SDA1: IC2.23, J1.3, J2.3, J6.3, R7.1
SDA2: IC3.23, J7.3, J8.3, J9.3, R12.1
SDA3: IC4.23, J10.3, J11.3, J12.3, R17.1
SDA4: IC5.23, J13.3, J14.3, J15.3, R22.1
SDA5: IC6.23, J16.3, J17.3, J18.3, R27.1
SDA6: IC7.23, J19.3, J20.3, J21.3, R32.1
SDA7: IC8.23, J22.3, J23.3, J24.3, R37.1
SDA8: IC9.23, J25.3, J26.3, J27.3, R42.1
SDA9: IC10.23, J28.3, J29.3, J30.3, R47.1
SDA10: IC11.23, J31.3, J32.3, J33.3, R52.1
SDA11: IC12.23, J34.3, J35.3, J36.3, R57.1
SDA12: IC13.23, J37.3, J38.3, J39.3, R62.1
SDA13: IC14.23, J40.3, J41.3, J42.3, R67.1
SDA14: IC15.23, J43.3, J44.3, J45.3, R72.1
SDA15: IC16.23, J46.3, J47.3, J48.3, R77.1
SDA16: IC17.23, J49.3, J50.3, J51.3, R82.1
SDA17: IC18.23, J52.3, J53.3, J54.3, R87.1
SDA18: IC19.23, J55.3, J56.3, J57.3, R92.1
SDA19: IC20.23, J58.3, J59.3, J60.3, R97.1
SDA20: IC21.23, J61.3, J62.3, J63.3, R102.1
SDA21: IC22.23, J64.3, J65.3, J66.3, R107.1
SDA22: IC23.23, J67.3, J68.3, J69.3, R112.1
SDA23: IC24.23, J70.3, J71.3, J72.3, R117.1
SDA24: IC25.23, J73.3, J74.3, J75.3, R122.1

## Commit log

2019-07-24 Created Board Layout and Schematic
2019-07-24 New Board Layout
    The pins were remapped with the LED Driver and the Display to create a better board layout.
2019-07-25 Created new Board
    Recreated the board in the new Branch with different pin mappings between the HT16K33 and the LED Display for easier routing
2019-07-25 Added Panelized Board and Gerber Files
    Updated the HT16K33 Footprint, fixed the board files to match the footprint, added the panelized production board and gerber files for ordering the board
2019-07-26 Moved Decoupling Cap
    Moved the decoupling capacitor next to the LED driver to resolve the GitHub issue
2019-07-26 Update README.md and added Document Folder
2020-02-03 New pin assignments
    Next: route address jumpers, etc
2020-02-06 Rev X02 of Qwiic Alpha?
    Still needs Nate's look-over. Tighter layout, mounting holes, address/power jumpers. Needs V score lines? Where will the silkscreen go?
2020-02-07 Rev X02 ordered!
2020-02-19 Added missing product ID's
2020-03-03 Add datasheet
2020-03-03 Rename jumpers to A0/A1/
2020-03-09 New decoupling cap
2020-03-10 Added extra decoupling cap
2020-03-18 Created script to mass test alphanumeric displays
2020-03-18 Generated files for product pages
2020-03-19 Corrected sch/brd files and production outputs
    I seemed to not have the right version of this board when I was wordking from home. Luckily, I had uploaded the files with the double decoupling caps to Sparkle. So I pulled those and fixed this repo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
2020-03-19 Generated new .pdf of schematic
    With double decoupling caps
2020-07-16 Added display datasheets
